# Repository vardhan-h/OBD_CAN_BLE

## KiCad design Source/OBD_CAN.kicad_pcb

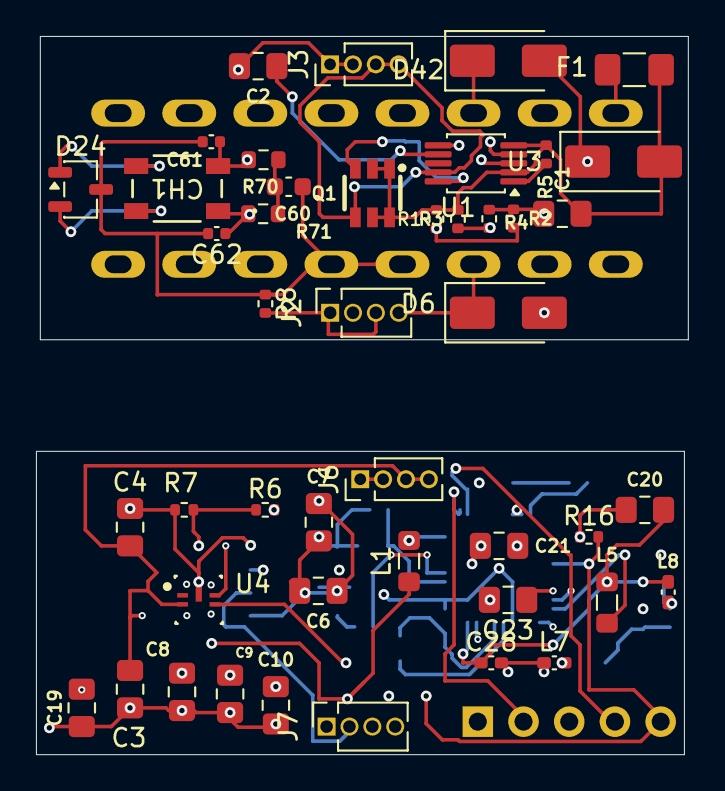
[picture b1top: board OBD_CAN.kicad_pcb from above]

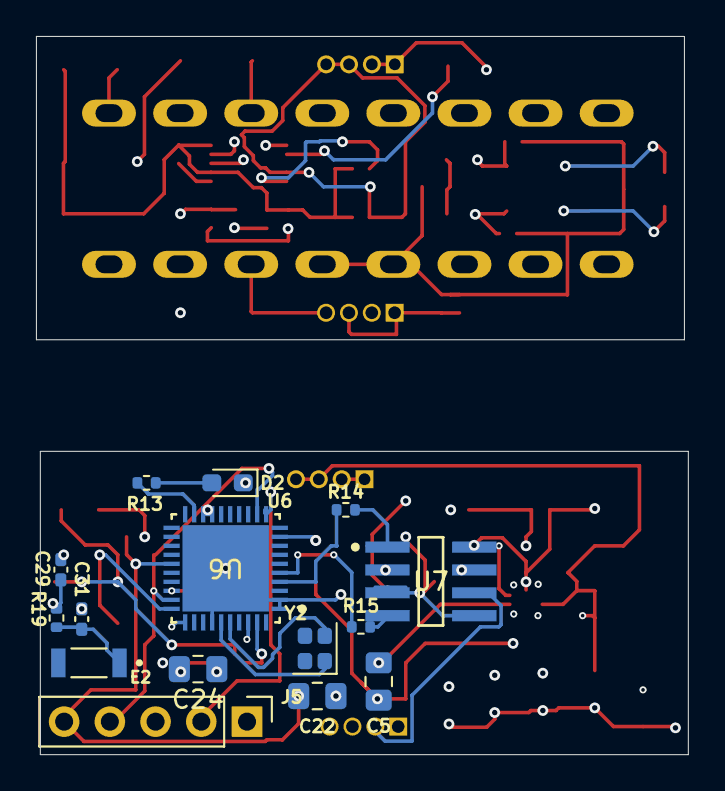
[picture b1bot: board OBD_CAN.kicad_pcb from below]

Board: 4 copper layers, 36.2 x 39.9 mm, 61 parts (16 on the bottom side), 37 nets.

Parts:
C1, C2, C4, C20, C22: 100nf; C_0805_2012Metric_Pad1.18x1.45mm_HandSolder
C3: 4.7uF; C_0805_2012Metric_Pad1.18x1.45mm_HandSolder
C5: 0.1uF; C_0805_2012Metric_Pad1.18x1.45mm_HandSolder
C6, C7: 22uF; C_0805_2012Metric_Pad1.18x1.45mm_HandSolder
C8, C9, C10: 47uf; C_0805_2012Metric_Pad1.18x1.45mm_HandSolder
C19: 1uF; C_0805_2012Metric_Pad1.18x1.45mm_HandSolder
C21, C24: 10uf; C_0805_2012Metric_Pad1.18x1.45mm_HandSolder
C23: 1uf; C_0805_2012Metric_Pad1.18x1.45mm_HandSolder
C28: 0.82pf; C_0402_1005Metric_Pad0.74x0.62mm_HandSolder
C29: 1.2pf; C_0402_1005Metric_Pad0.74x0.62mm_HandSolder
C31: DNM; C_0402_1005Metric_Pad0.74x0.62mm_HandSolder
C60: 1nF 100V 0603; C_0603_1608Metric
C61, C62: 100pF 100V 0402; C_0402_1005Metric
CH1: ACT45B-510-2P-TL003; IND_ACT45R_TDK
D2: STATUS_LED; LED_0603_1608Metric_Pad1.05x0.95mm_HandSolder
D6, D42: SMAJ24CA; D_SMA
D24: ESD2CAN24-Q1; SOT-23-3
E2: 2450AT18B100E; XDCR_2450AT18B100E
F1: PTC_2A; Fuse_1206_3216Metric_Pad1.42x1.75mm_HandSolder
J2: Conn_01x04_Pin; PinSocket_1x04_P1.27mm_Vertical
J3: Conn_01x04_Socket; PinHeader_1x04_P1.27mm_Vertical
J5: SWD_DEBUG; PinHeader_1x05_P2.54mm_Vertical
J6: Conn_01x04_Pin; PinHeader_1x04_P1.27mm_Vertical
J7: Conn_01x04_Socket; PinSocket_1x04_P1.27mm_Vertical
L1: 4.7uH; L_0805_2012Metric_Pad1.05x1.20mm_HandSolder
L5: 6.8µH; L_0805_2012Metric_Pad1.05x1.20mm_HandSolder
L7: 1.1nH; L_0402_1005Metric_Pad0.77x0.64mm_HandSolder
L8: 3.4nH; L_0402_1005Metric_Pad0.77x0.64mm_HandSolder
M1: OBDII
Q1: FDC3512; SOT-23-6_L2.9-W1.6-P0.95-LS2.8-BR
R1: 150k; R_0402_1005Metric
R2, R16: 10k; R_0402_1005Metric
R3: 75k; R_0402_1005Metric
R4: 20k; R_0402_1005Metric
R5: 5.6k; R_0402_1005Metric
R6: 33.2k; R_0402_1005Metric
R7: 14.3k; R_0402_1005Metric
R8: 0E; R_0402_1005Metric
R13: 1k; R_0402_1005Metric
R14, R15, R19: 0; R_0402_1005Metric
R70, R71: 60.4R 0603; R_0603_1608Metric
U1: LM5060; MSOP-10_3x3mm_P0.5mm
U3: SMAJ5.0CA; D_SMA
U4: LMR43610R3RPER; RPE0009A-MFG
U6: CC2745R10E0WRHARQ1; RHA0040T-IPC_A
U7: TCAN1044AVDRQ1; D0008A-IPC_A
Y2: 48MHz; Crystal_SMD_2016-4Pin_2.0x1.6mm

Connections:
+3.3V: C6.2, C7.2, C8.2, C9.2, C10.2, C20.1, C24.1, J5.1, L1.2, R6.2, R16.1, U6.9 (VDDIO), U6.17 (VDDIO), U6.18 (VDDS), U6.29 (VDDS), U6.31 (VDDS), U6.38 (VDDS), U7.3 (VCC), U7.5 (VIO)
/Bottom_PCB/VBAT_FUSED: C1.2, F1.2, Q1.1 (D), Q1.2 (D), Q1.5 (D), Q1.6 (D), R1.1, R3.1, R5.1, U1.2 (VIN), U1.5 (EN), U3.2 (A2)
/Bottom_PCB/VBAT_OBD: F1.1, M1.16 (BATTPOWER)
/Top_PCB/RSTN: C22.2, J5.5, R16.2, U6.25 (RST_N)
/Top_PCB/SWDCK: J5.4, U6.12 (DIO10_SWDCK)
/Top_PCB/SWDIO: J5.2, U6.11 (DIO9_SWDIO)
CAN0RX: R15.2, U7.4 (RXD)
CAN0TX: R14.1, U7.1 (TXD)
CANH: CH1.4 (Pri-), D24.2
CANL: CH1.3 (Sec-), D24.1
CAN_H: C62.1, CH1.1 (Pri+), D6.1 (A1), J2.4, J7.4, M1.6 (CANHIGH), R71.2, U7.7 (CANH)
CAN_L: C61.2, CH1.2 (Sec+), D42.1 (A1), J2.2, J7.2, M1.14 (CANLOW), R70.1, U7.6 (CANL)
GND: C1.1, C2.2, C3.2, C4.2, C6.1, C7.1, C8.1, C9.1, C10.1, C19.2, C20.2, C21.1, C21.2, C22.1, C23.2, C24.2, C29.1, C31.1, D2.1 (K), J2.1, J2.3, J3.1, J3.2, J5.3, J6.1, J6.2, J7.1, J7.3, L5.1, L7.2, R2.2, R4.2, R7.1, R8.2, U1.6 (GND), U4.1 (RT), U4.9 (GND), U6.1 (VDDR), U6.2 (VDDR), U6.34 (VDDR), U6.41 (EGP), U7.2 (GND), U7.8 (STB)
GNDPWR: C60.2, C61.1, C62.2, D6.2 (A2), D24.3, D42.2 (A2), M1.4 (CHASGND), M1.5 (SIGGND), R8.1, U3.1 (A1)
unnamed: C28.2, L7.1
unnamed: C29.2, L8.2, R19.1
unnamed: C31.2, E2.1, R19.2
unnamed: C60.1, R70.2, R71.1
unnamed: D2.2 (A), R13.1
unnamed: Q1.3 (G), U1.10 (GATE)
unnamed: R1.2, R2.1, U1.3 (OVP)
unnamed: R5.2, U1.1 (SENSE)
unnamed: C2.1, U1.7 (TIMER)
unnamed: R3.2, R4.1, U1.4 (UVLO)
unnamed: C5.1, U4.6 (BOOT)
unnamed: C5.2, L1.1, U4.5 (SW)
unnamed: C19.1, U4.7 (VCC)
unnamed: R6.1, R7.2, U4.8 (VOUT_FB)
unnamed: C28.1, L8.1, U6.39 (ANT)
unnamed: L5.2, U6.30 (DCDC)
unnamed: R14.2, U6.4 (DIO1)
unnamed: R15.1, U6.5 (DIO2)
unnamed: R13.2, U6.19 (DIO17_A8)
unnamed: C23.1, U6.28 (VDDD)
unnamed: U6.36 (X48N), Y2.2
unnamed: U6.35 (X48P), Y2.1
VBAT_PROTECTED: C3.1, C4.1, J3.3, J3.4, J6.3, J6.4, Q1.4 (S), U1.9 (OUT), U4.3 (EN_UVLO), U4.4 (VIN)
